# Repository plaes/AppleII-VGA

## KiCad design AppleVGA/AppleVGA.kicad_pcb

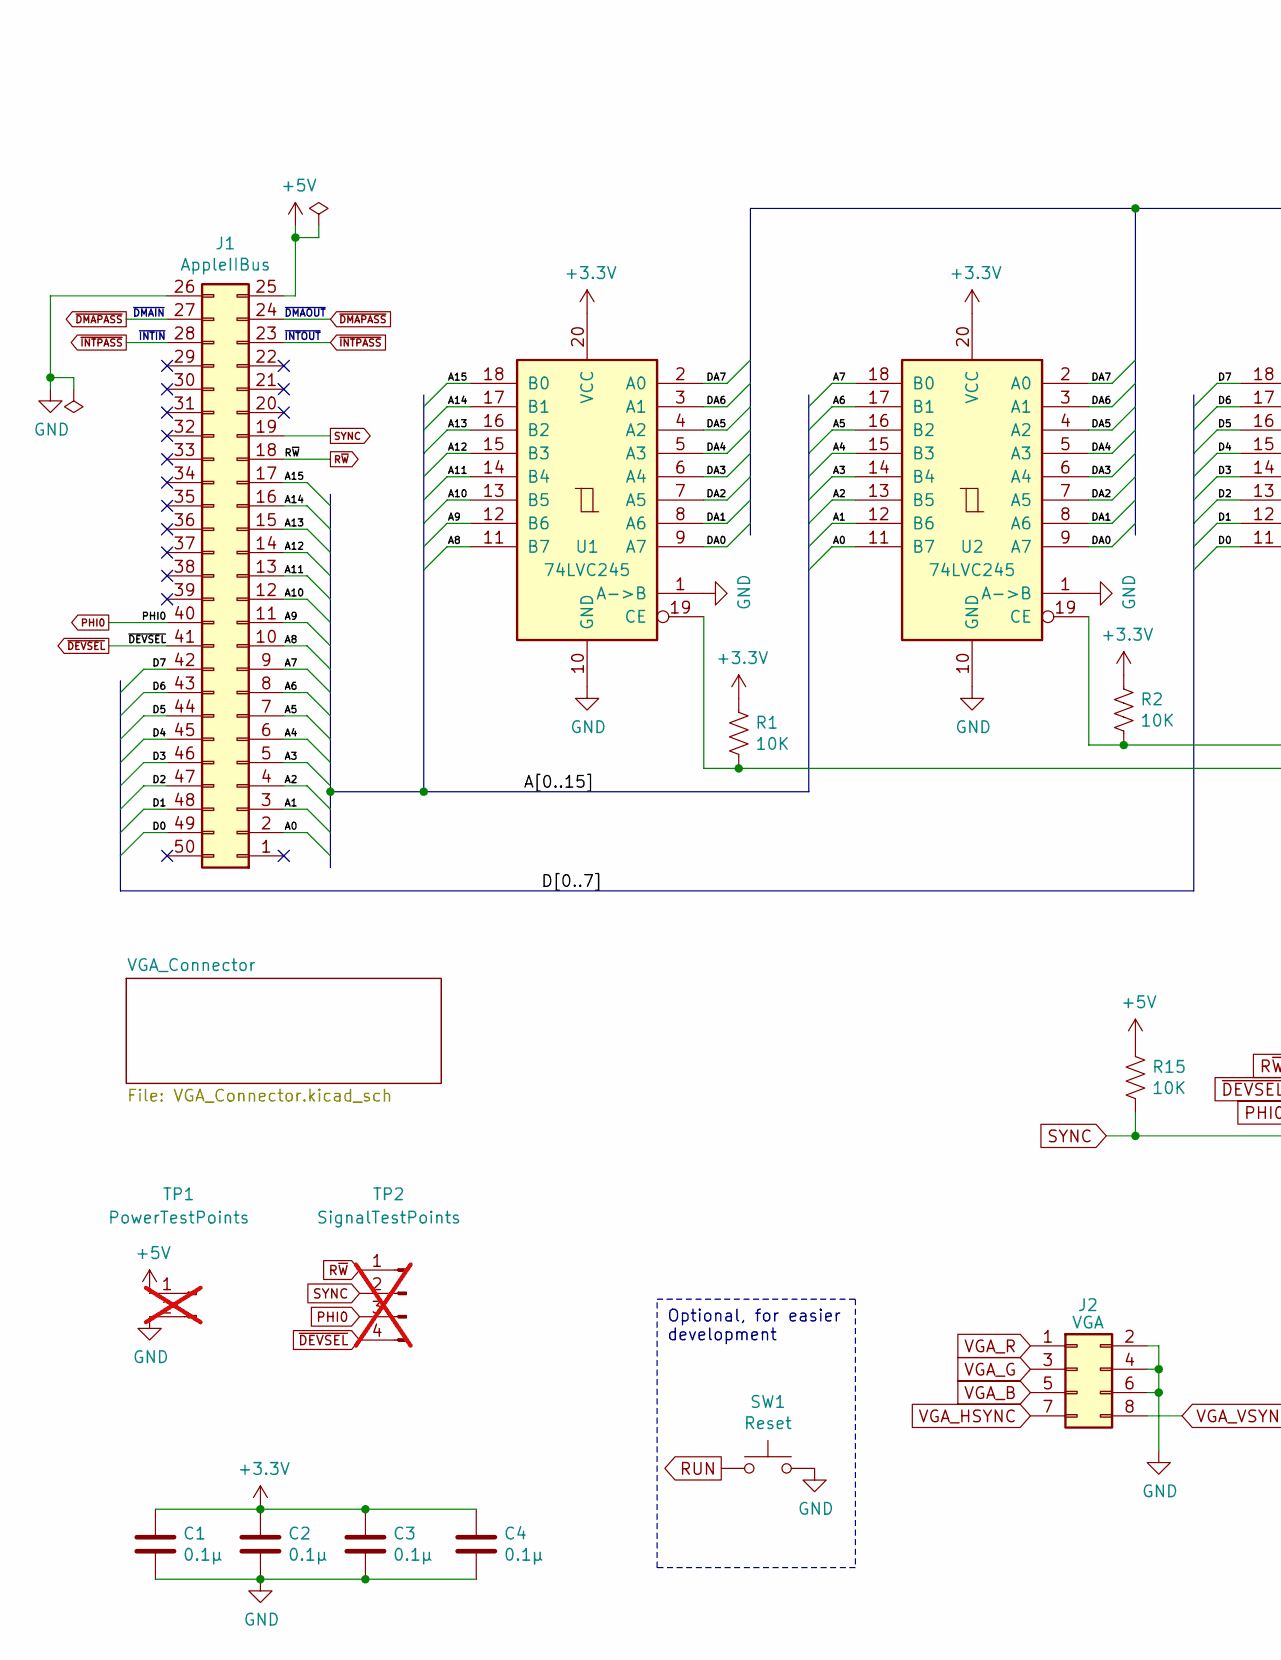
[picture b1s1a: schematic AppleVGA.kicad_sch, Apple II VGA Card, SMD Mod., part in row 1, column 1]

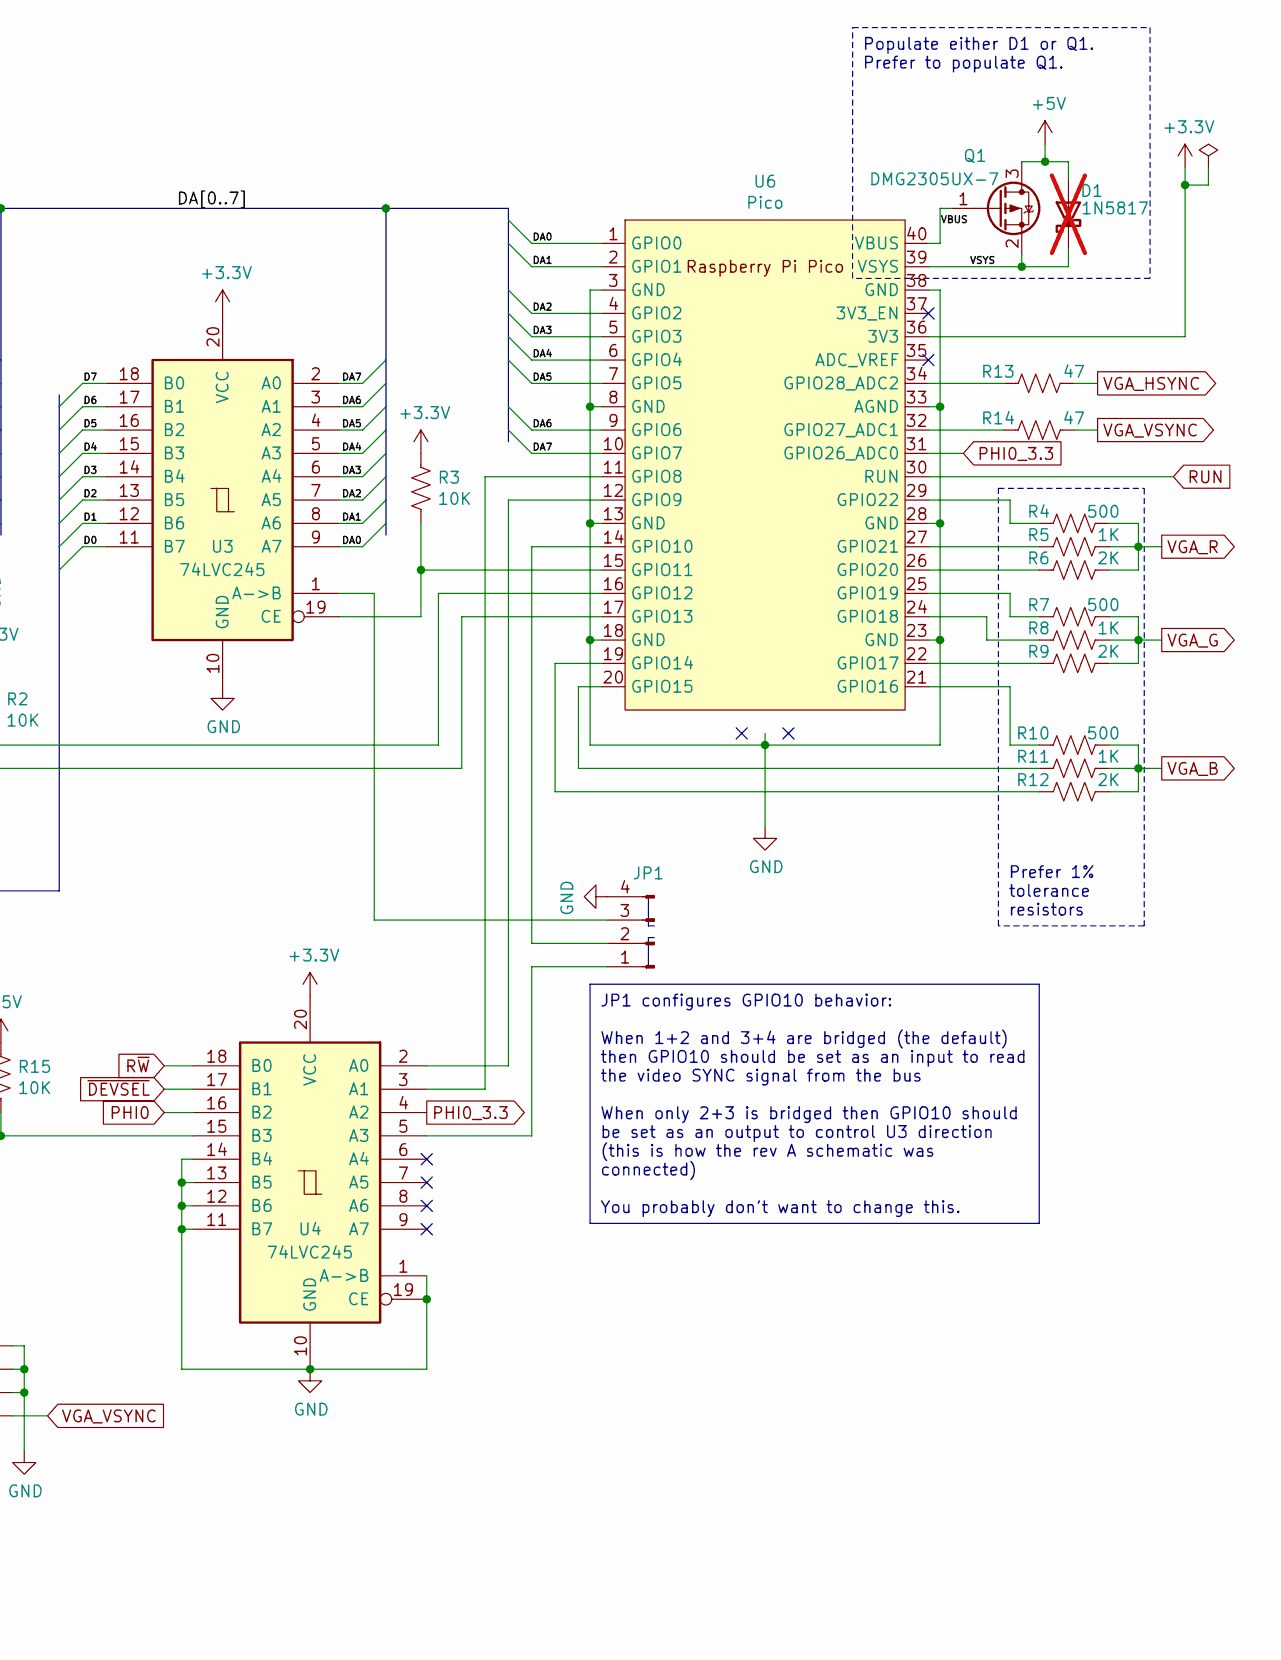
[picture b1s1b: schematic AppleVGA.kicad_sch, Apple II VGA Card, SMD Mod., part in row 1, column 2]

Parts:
C1, C2, C3, C4: 0.1μ; C_0603_1608Metric_Pad1.08x0.95mm_HandSolder; MouserNo 594-A104K15X7RF5TAA
D1: 1N5817; D_0603_1608Metric_Pad1.05x0.95mm_HandSolder; MouserNo 511-1N5817; not fitted
J1: AppleIIBus; AppleIIBus_Edge
J2: VGA; IDC-Header_2x04_P2.54mm_Horizontal; MouserNo 649-75869-232LF
JP1: JumperPads; SolderJumper-4_P1.3mm_Bridged12_34_RoundedPad1.0x1.5mm_Numb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
Q1: DMG2305UX-7; SOT-23; MouserNo 621-DMG2305UX-7
R1, R2, R3, R15: 10K; R_0603_1608Metric_Pad0.98x0.95mm_HandSolder; MouserNo 603-CFR-25JR-5210K
R4, R7, R10: 500; R_0603_1608Metric_Pad0.98x0.95mm_HandSolder; MouserNo 603-MFR-25FBF52-499R
R5, R8, R11: 1K; R_0603_1608Metric_Pad0.98x0.95mm_HandSolder; MouserNo 603-MFR-25FBF52-1K
R6, R9, R12: 2K; R_0603_1608Metric_Pad0.98x0.95mm_HandSolder; MouserNo 603-MFR-25FBF52-2K
R13, R14: 47; R_0603_1608Metric_Pad0.98x0.95mm_HandSolder; MouserNo 603-MFR-25FTF52-47R
SW1: Reset; TS-1187A-B-A-B; MouserNo 506-FSM4JH
TP1: PowerTestPoints; PinHeader_1x02_P2.54mm_Vertical; not fitted
TP2: SignalTestPoints; PinHeader_1x04_P2.54mm_Vertical; not fitted
U1, U2, U3, U4: 74LVC245; SOIC-20W_7.5x12.8mm_P1.27mm; MouserNo 595-SN74LVC245AN
U6: Pico; RPi_Pico_H_SMD_TH

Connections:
+3.3V: C1.1, C2.1, C3.1, C4.1, R1.1, R2.1, R3.1, U1.20 (VCC), U2.20 (VCC), U3.20 (VCC), U4.20 (VCC), U6.36 (3V3)
+5V: D1.2 (A), J1.25, Q1.3 (D), R15.1, TP1.1
/A0: J1.2, U2.11 (B7)
/A1: J1.3, U2.12 (B6)
/A2: J1.4, U2.13 (B5)
/A3: J1.5, U2.14 (B4)
/A4: J1.6, U2.15 (B3)
/A5: J1.7, U2.16 (B2)
/A6: J1.8, U2.17 (B1)
/A7: J1.9, U2.18 (B0)
/A8: J1.10, U1.11 (B7)
/A9: J1.11, U1.12 (B6)
/A10: J1.12, U1.13 (B5)
/A11: J1.13, U1.14 (B4)
/A12: J1.14, U1.15 (B3)
/A13: J1.15, U1.16 (B2)
/A14: J1.16, U1.17 (B1)
/A15: J1.17, U1.18 (B0)
/D0: J1.49, U3.11 (B7)
/D1: J1.48, U3.12 (B6)
/D2: J1.47, U3.13 (B5)
/D3: J1.46, U3.14 (B4)
/D4: J1.45, U3.15 (B3)
/D5: J1.44, U3.16 (B2)
/D6: J1.43, U3.17 (B1)
/D7: J1.42, U3.18 (B0)
/DA0: U1.9 (A7), U2.9 (A7), U3.9 (A7), U6.1 (GPIO0)
/DA1: U1.8 (A6), U2.8 (A6), U3.8 (A6), U6.2 (GPIO1)
/DA2: U1.7 (A5), U2.7 (A5), U3.7 (A5), U6.4 (GPIO2)
/DA3: U1.6 (A4), U2.6 (A4), U3.6 (A4), U6.5 (GPIO3)
/DA4: U1.5 (A3), U2.5 (A3), U3.5 (A3), U6.6 (GPIO4)
/DA5: U1.4 (A2), U2.4 (A2), U3.4 (A2), U6.7 (GPIO5)
/DA6: U1.3 (A1), U2.3 (A1), U3.3 (A1), U6.9 (GPIO6)
/DA7: U1.2 (A0), U2.2 (A0), U3.2 (A0), U6.10 (GPIO7)
/VBUS: Q1.1 (G), U6.40 (VBUS)
/VSYS: D1.1 (K), Q1.2 (S), U6.39 (VSYS)
GND: C1.2, C2.2, C3.2, C4.2, J1.26, J2.2, J2.4, J2.6, JP1.4, SW1.2, TP1.2, U1.1 (A->B), U1.10 (GND), U2.1 (A->B), U2.10 (GND), U3.10 (GND), U4.1 (A->B), U4.10 (GND), U4.11 (B7), U4.12 (B6), U4.13 (B5), U4.14 (B4), U4.19 (CE), U6.3 (GND), U6.8 (GND), U6.13 (GND), U6.18 (GND), U6.23 (GND), U6.28 (GND), U6.33 (AGND), U6.38 (GND)
unnamed: JP1.1, U4.5 (A3)
unnamed: JP1.2, U6.14 (GPIO10)
unnamed: JP1.3, U3.1 (A->B)
unnamed: R1.2, U1.19 (CE), U6.17 (GPIO13)
unnamed: R2.2, U2.19 (CE), U6.16 (GPIO12)
unnamed: R3.2, U3.19 (CE), U6.15 (GPIO11)
unnamed: U4.2 (A0), U6.12 (GPIO9)
unnamed: U4.3 (A1), U6.11 (GPIO8)
unnamed: R12.1, U6.19 (GPIO14)
unnamed: R11.1, U6.20 (GPIO15)
unnamed: R10.1, U6.21 (GPIO16)
unnamed: R9.1, U6.22 (GPIO17)
unnamed: R8.1, U6.24 (GPIO18)
unnamed: R7.1, U6.25 (GPIO19)
unnamed: R6.1, U6.26 (GPIO20)
unnamed: R5.1, U6.27 (GPIO21)
unnamed: R4.1, U6.29 (GPIO22)
unnamed: R14.1, U6.32 (GPIO27_ADC1)
unnamed: R13.1, U6.34 (GPIO28_ADC2)
PHI0: J1.40, TP2.3, U4.16 (B2)
PHI0_3.3: U4.4 (A2), U6.31 (GPIO26_ADC0)
RUN: SW1.1, U6.30 (RUN)
R~W: J1.18, TP2.1, U4.18 (B0)
SYNC: J1.19, R15.2, TP2.2, U4.15 (B3)
VGA_B: J2.5, R10.2, R11.2, R12.2
VGA_G: J2.3, R7.2, R8.2, R9.2
VGA_HSYNC: J2.7, R13.2
VGA_R: J2.1, R4.2, R5.2, R6.2
VGA_VSYNC: J2.8, R14.2
~DEVSEL: J1.41, TP2.4, U4.17 (B1)
~DMAPASS: J1.24, J1.27
~INTPASS: J1.23, J1.28

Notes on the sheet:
Optional, for easier development
Populate either D1 or Q1. Prefer to populate Q1.
JP1 configures GPIO10 behavior: When 1+2 and 3+4 are bridged (the default) then GPIO10 should be set as an input to read the video SYNC signal from the bus When only 2+3 is bridged then GPIO10 should be set as an output to control U3 direction (this is how the rev A schematic was connected) You pro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
Prefer 1% tolerance resistors
~{DMAIN}
~{INTOUT}
~{DMAOUT}
~{INTIN}

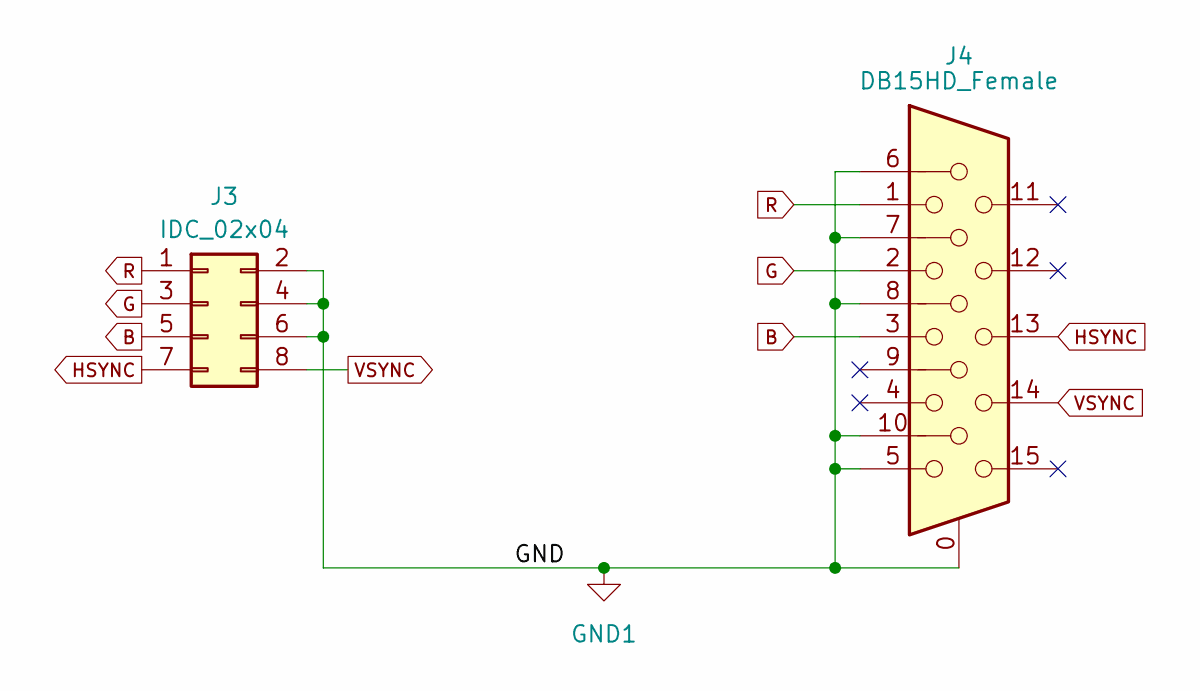
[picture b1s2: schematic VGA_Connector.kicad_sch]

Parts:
J3: IDC_02x04; IDC-Header_2x04_P2.54mm_Vertical; MouserNo 649-75869-232LF
J4: DB15HD_Female; DSUB-15HD_TE_Connectivity_2311586-4; MouserNo 571-2311586-4

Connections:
B: J3.5, J4.3
G: J3.3, J4.2
GND1: J3.2, J3.4, J3.6, J4.0, J4.5, J4.6, J4.7, J4.8, J4.10
HSYNC: J3.7, J4.13
R: J3.1, J4.1
VSYNC: J3.8, J4.14

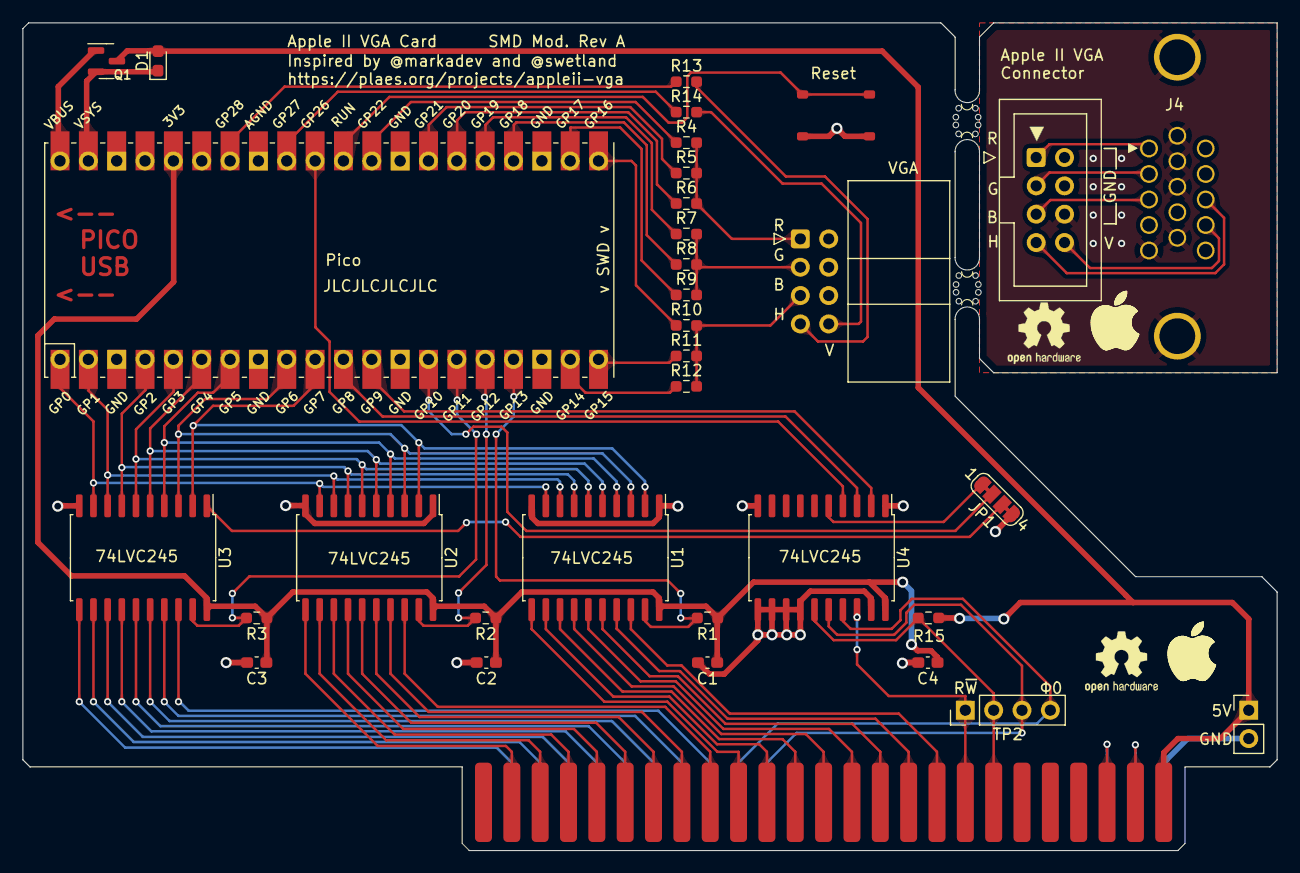
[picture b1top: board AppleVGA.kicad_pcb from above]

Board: 2 copper layers, 112.4 x 74.2 mm, 38 parts (0 on the bottom side), 75 nets.

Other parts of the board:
LOGO1, LOGO1#2: AppleLogo_5mm
mouse-bite-1mm-slot, mouse-bite-1mm-slot#2: VAL**; mouse-bite-1mm-slot

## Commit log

2024-01-29 pcb-smd: Add various required footprints
2024-01-29 pcb-smd: Add new SMD-mod board + breakoff VGA board
2024-01-29 pcb-smd: List changes and add manufacturing outputs.
2024-02-09 Add JLCJLCJLC text for order placement text

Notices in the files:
AppleVGA/AppleVGA.kicad_pcb:
Licensed under CERN-OHL-P V2.0 (https://ohwr.org/cern_ohl_p_v2.txt)
Copyright (c) 2021-2023 Mark Aikens
AppleVGA/AppleVGA.kicad_sch:
Copyright (c) 2024 Priit Laes
